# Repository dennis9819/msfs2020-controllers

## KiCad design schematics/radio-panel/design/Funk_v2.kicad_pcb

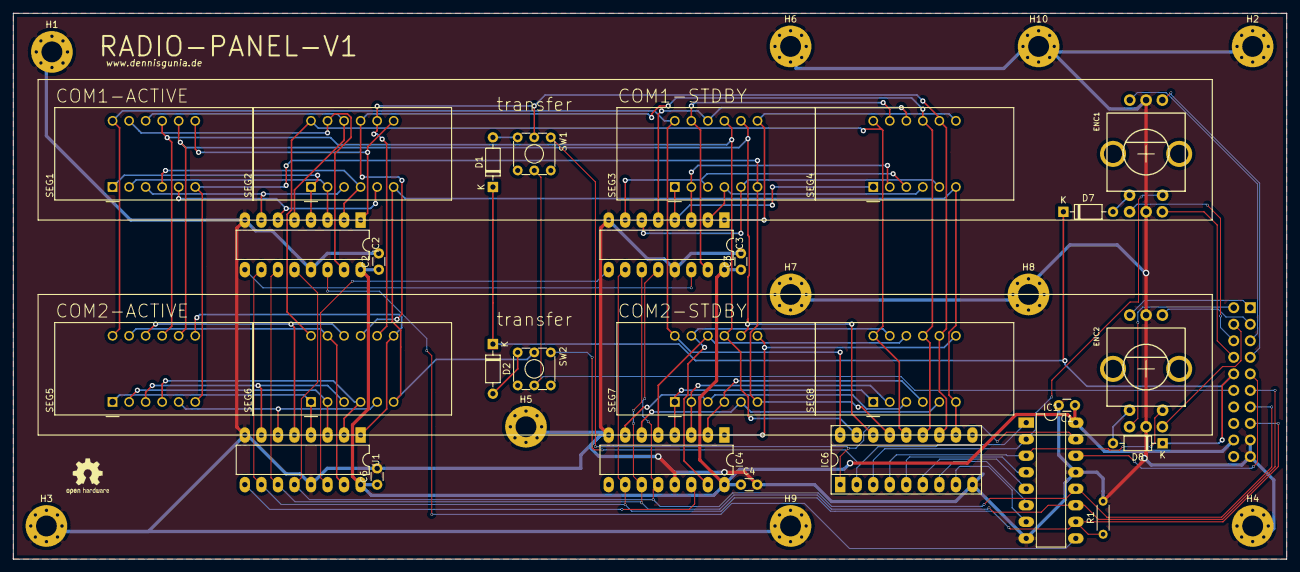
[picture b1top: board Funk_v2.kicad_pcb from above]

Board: 2 copper layers, 195.6 x 83.8 mm, 39 parts (1 on the bottom side), 72 nets.

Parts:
C1, C2, C3, C4, C6: 100nF; C_Disc_D3.0mm_W1.6mm_P2.50mm
D1, D2, D7, D8: 1N4148; D_DO-35_SOD27_P7.62mm_Horizontal
ENC1, ENC2: Alps_EC11; dual_EC11_SW
H1, H2, H3, H4, H5, H6, H7, H8, H9, H10: MountingHole; MountingHole_3.2mm_M3_Pad_Via
IC1, IC2, IC3, IC4: 74AHC595; DIP-16_W7.62mm_LongPads
IC6: ULN2803A; DIP-18_W7.62mm_Socket_LongPads
J1: Conn_02x09_Odd_Even; Multicomp_MC9A12-2034_2x10_P2.54mm_Vertical
R1: 10K; R_Axial_DIN0204_L3.6mm_D1.6mm_P5.08mm_Horizontal
SEG1, SEG5, SEG6, SEG7, SEG8: CC56-12SRWA; 7seg-056
SEG2, SEG3, SEG4: TS5:7seg-056; 7seg-056
SW1, SW2: TS5
U1: 74AHC595; DIP-16_W7.62mm_LongPads

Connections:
+5V: C1.1, C2.1, C3.1, C4.1, C6.1, IC1.16, IC2.16, IC3.16, IC4.16, J1.18, U1.16
/BTN_MUX: D1.1, D2.1, D7.1, D8.1, J1.10
/DIG1: IC6.18, SEG1.12, SEG3.12, SEG5.12, SEG7.12
/DIG2: IC6.17, SEG1.9, SEG3.9, SEG5.9, SEG7.9
/DIG3: IC6.16, SEG1.8, SEG3.8, SEG5.8, SEG7.8
/DIG4: IC6.15, SEG1.6, SEG3.6, SEG5.6, SEG7.6
/DIG5: IC6.14, SEG2.12, SEG4.12, SEG6.12, SEG8.12
/DIG6: IC6.13, SEG2.9, SEG4.9, SEG6.9, SEG8.9
/DIG7: IC6.12, SEG2.8, SEG4.8, SEG6.8, SEG8.8, SW1.3
/DIG8: IC6.11, SEG2.6, SEG4.6, SEG6.6, SEG8.6, SW2.3
/LED_BTN: J1.12, SW1.4, SW2.4
BTN1: IC1.15, IC6.1, SW1.1
BTN2: IC1.1, IC6.2, SW2.1
BTN3: ENC1.7, IC1.2, IC6.3
BTN4: ENC2.7, IC1.3, IC6.4
GND: C1.2, C2.2, C3.2, C4.2, C6.2, ENC1.3, ENC1.6, ENC2.3, ENC2.6, H1.1, H2.1, H3.1, H4.1, H5.1, H6.1, H7.1, H8.1, H9.1, H10.1, IC1.8, IC1.13, IC2.8, IC2.13, IC3.8, IC3.13, IC4.8, IC4.13, IC6.9, J1.17, J1.19, R1.2, U1.8, U1.13
LCLK: IC1.12, IC2.12, IC3.12, IC4.12, J1.13, U1.12
unnamed: D1.2, SW1.2
unnamed: D2.2, SW2.2
unnamed: D7.2, ENC1.8
unnamed: D8.2, ENC2.8
unnamed: ENC1.1, J1.7
unnamed: ENC1.2, J1.5
unnamed: ENC1.4, J1.8
unnamed: ENC1.5, J1.6
unnamed: ENC2.1, J1.3
unnamed: ENC2.2, J1.1
unnamed: ENC2.4, J1.4
unnamed: ENC2.5, J1.2
unnamed: IC1.4, IC6.5
unnamed: IC1.5, IC6.6
unnamed: IC1.6, IC6.7
unnamed: IC1.7, IC6.8
unnamed: IC2.1, SEG1.7, SEG2.7
unnamed: IC2.2, SEG1.4, SEG2.4
unnamed: IC2.3, SEG1.2, SEG2.2
unnamed: IC2.4, SEG1.1, SEG2.1
unnamed: IC2.5, SEG1.10, SEG2.10
unnamed: IC2.6, SEG1.5, SEG2.5
unnamed: IC2.7, SEG1.3, SEG2.3
unnamed: IC2.15, SEG1.11, SEG2.11
unnamed: IC3.1, SEG3.7, SEG4.7
unnamed: IC3.2, SEG3.4, SEG4.4
unnamed: IC3.3, SEG3.2, SEG4.2
unnamed: IC3.4, SEG3.1, SEG4.1
unnamed: IC3.5, SEG3.10, SEG4.10
unnamed: IC3.6, SEG3.5, SEG4.5
unnamed: IC3.7, SEG3.3, SEG4.3
unnamed: IC3.15, SEG3.11, SEG4.11
unnamed: IC4.1, SEG7.7, SEG8.7
unnamed: IC4.2, SEG7.4, SEG8.4
unnamed: IC4.3, SEG7.2, SEG8.2
unnamed: IC4.4, SEG7.1, SEG8.1
unnamed: IC4.5, SEG7.10, SEG8.10
unnamed: IC4.6, SEG7.5, SEG8.5
unnamed: IC4.7, SEG7.3, SEG8.3
unnamed: IC4.15, SEG7.11, SEG8.11
unnamed: SEG5.1, SEG6.1, U1.4
unnamed: SEG5.2, SEG6.2, U1.3
unnamed: SEG5.3, SEG6.3, U1.7
unnamed: SEG5.4, SEG6.4, U1.2
unnamed: SEG5.5, SEG6.5, U1.6
unnamed: SEG5.7, SEG6.7, U1.1
unnamed: SEG5.10, SEG6.10, U1.5
unnamed: SEG5.11, SEG6.11, U1.15
RESET: IC1.10, IC2.10, IC3.10, IC4.10, J1.15, R1.1, U1.10
SDATA: IC1.14, J1.9
SDATA1: IC1.9, IC2.14
SDATA2: IC2.9, IC3.14
SDATA3: IC3.9, U1.14
SDATA4: IC4.14, U1.9
SDCLK: IC1.11, IC2.11, IC3.11, IC4.11, J1.11, U1.11

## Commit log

2021-06-21 init v1 radio panel
2021-06-21 fixed md name
2021-06-29 Update parts.md
    added missing parts
2021-06-29 added firmware for trim
2021-08-04 added altimeter firmware
2021-08-14 Working V1 - w/o QNH
2023-07-15 update repo
2023-07-15 changed a lot...
2025-07-06 push updates
